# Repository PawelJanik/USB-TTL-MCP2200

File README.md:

# USB-TTL-MCP2200
Simple conventer USB-TTL on MCP2200

More description on site: http://www.robotyka.net.pl/przejsciowka-usbttl-na-ukladzie-microchip-mcp2200/

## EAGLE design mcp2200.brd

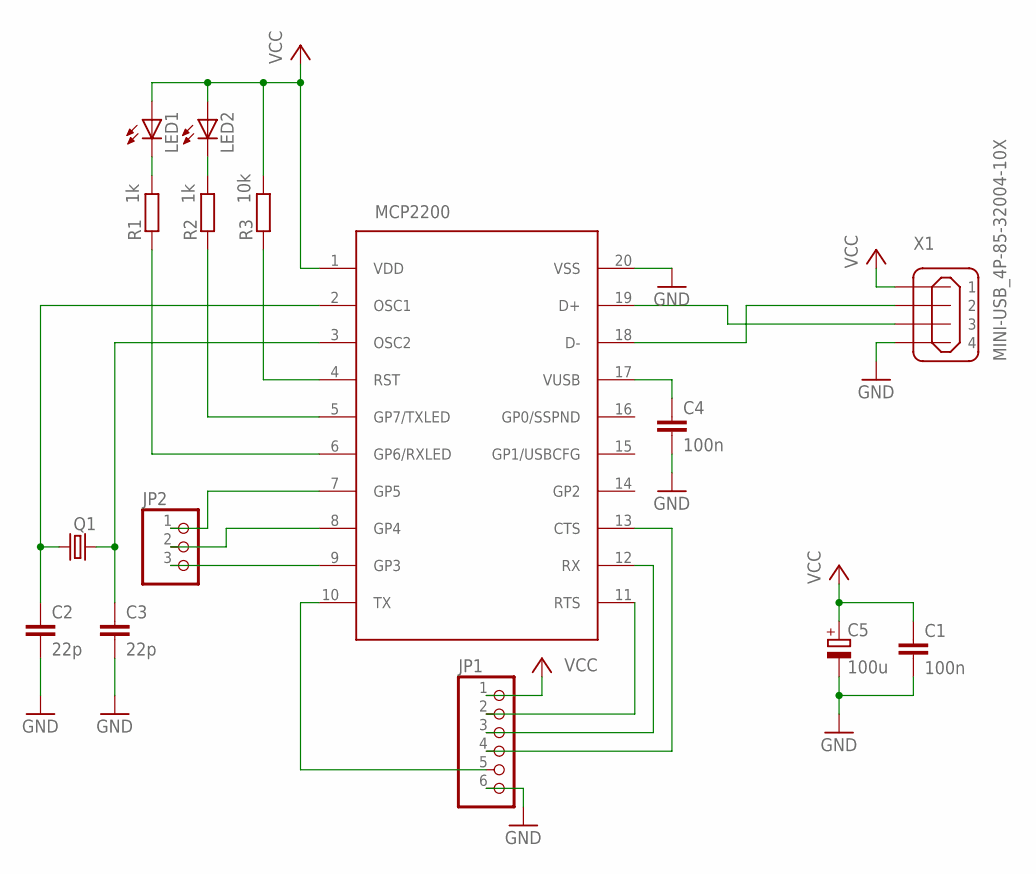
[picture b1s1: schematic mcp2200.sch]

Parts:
C1, C4: 100n; C025-025X050
C2, C3: 22p; C025-025X050
C5: 100u; E3,5-8
JP1: PINHD-1X6; 1X06
JP2: PINHD-1X3; 1X03
LED1, LED2: LED3MM
MCP2200: MCP2200; SOIC127P1032X265-20
Q1: CRYSTALHC49S; HC49/S
R1, R2: 1k; R1206
R3: 10k; R1206
X1: MINI-USB_4P-85-32004-10X; 85-32004-10X

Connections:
GND: C1.2, C2.2, C3.2, C4.2, C5.-, JP1.6, MCP2200.20 (VSS), X1.4
unnamed: LED2.K (C), R2.2
unnamed: LED1.K (C), R1.2
unnamed: MCP2200.5 (GP7/TXLED), R2.1
unnamed: MCP2200.6 (GP6/RXLED), R1.1
unnamed: C2.1, MCP2200.2 (OSC1), Q1.2
unnamed: C3.1, MCP2200.3 (OSC2), Q1.1
unnamed: MCP2200.4 (RST), R3.1
unnamed: MCP2200.18 (D-), X1.2
unnamed: MCP2200.19 (D+), X1.3
unnamed: C4.1, MCP2200.17 (VUSB)
unnamed: JP2.1, MCP2200.7 (GP5)
unnamed: JP2.2, MCP2200.8 (GP4)
unnamed: JP2.3, MCP2200.9 (GP3)
unnamed: JP1.5, MCP2200.10 (TX)
unnamed: JP1.4, MCP2200.13 (CTS)
unnamed: JP1.3, MCP2200.12 (RX)
unnamed: JP1.2, MCP2200.11 (RTS)
VCC: C1.1, C5.+, JP1.1, LED1.A, LED2.A, MCP2200.1 (VDD), R3.2, X1.1

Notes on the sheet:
MCP2200

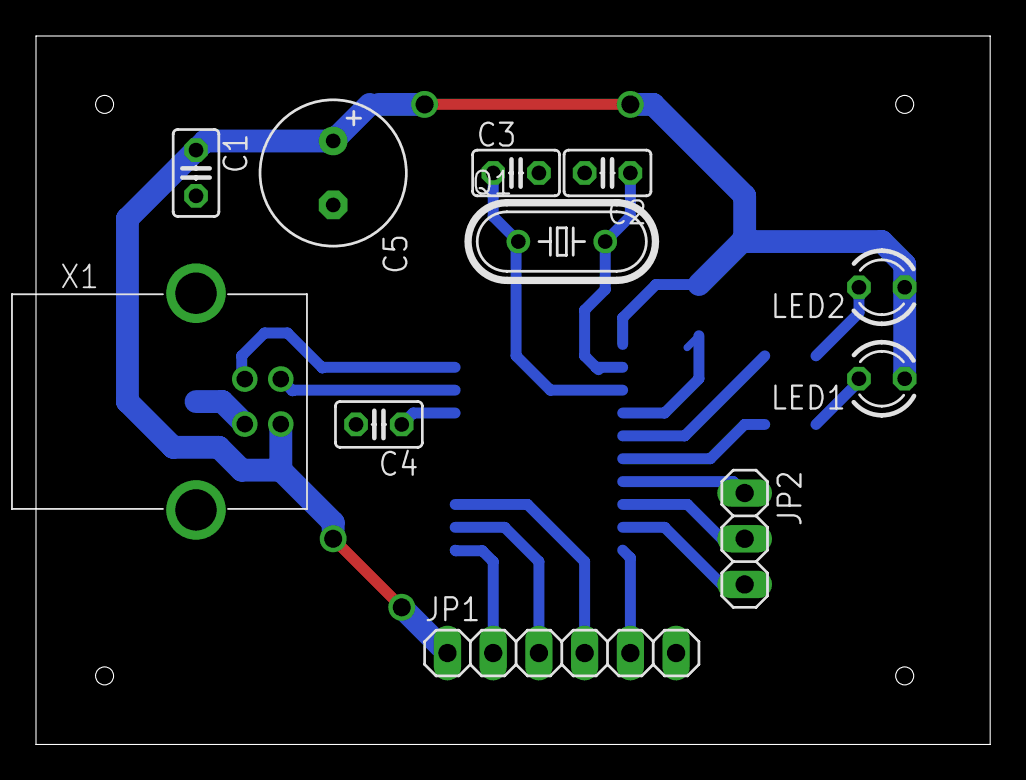
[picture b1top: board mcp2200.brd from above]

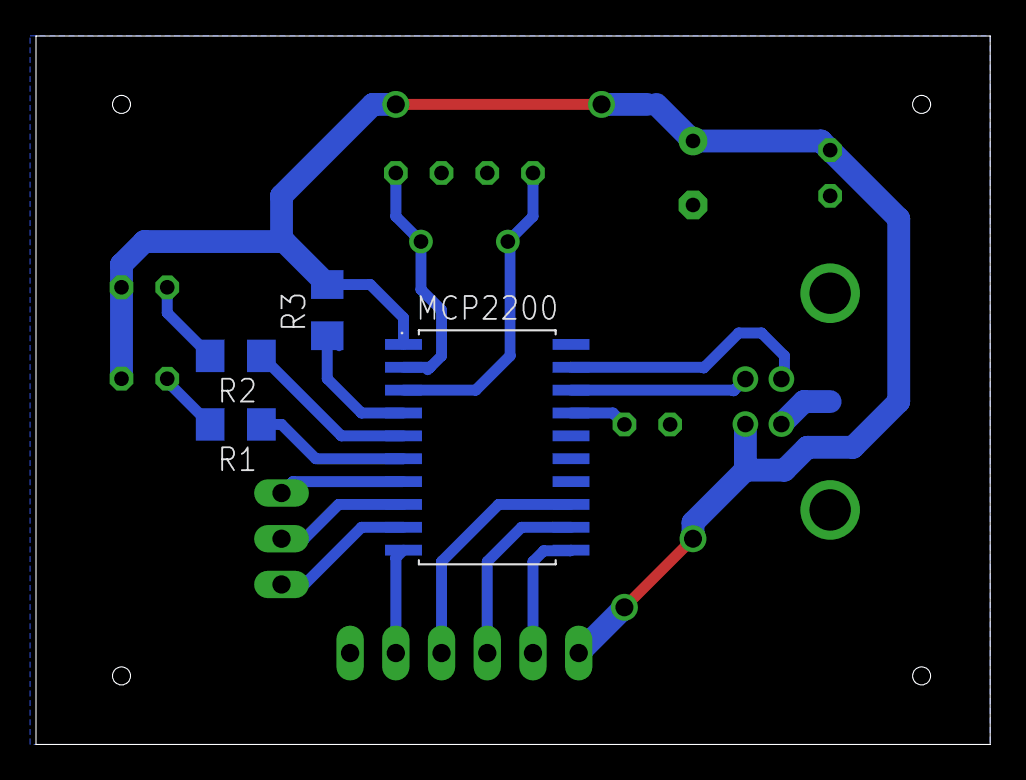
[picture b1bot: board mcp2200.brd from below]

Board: 2 copper layers, 53.0 x 39.4 mm, 15 parts (4 on the bottom side), 19 nets.

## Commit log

2018-05-19 Project Board with mcp2200
    Eagle files and photos of prototype.
